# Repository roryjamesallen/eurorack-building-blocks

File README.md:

# eurorack-building-blocks
 A collection of building block circuits for eurorack

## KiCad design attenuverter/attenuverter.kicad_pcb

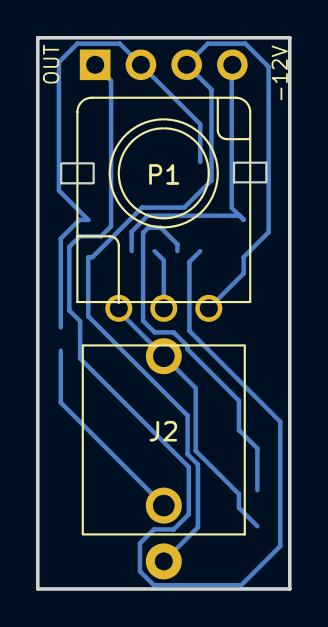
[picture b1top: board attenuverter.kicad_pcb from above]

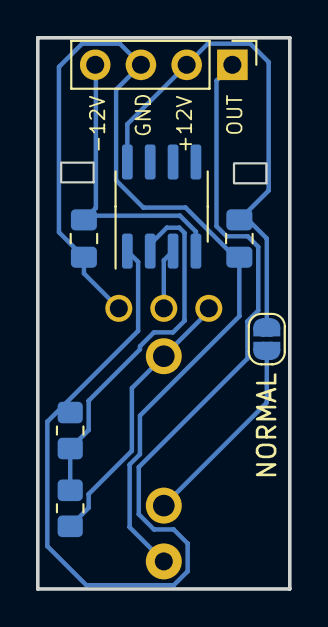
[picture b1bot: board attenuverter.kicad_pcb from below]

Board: 2 copper layers, 14.0 x 30.6 mm, 9 parts (7 on the bottom side), 8 nets.

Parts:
C1, C2: 100n; C_0805_2012Metric_Pad1.18x1.45mm_HandSolder
CONN1: Conn_01x04_Male; PinHeader_1x04_P2.54mm_Vertical
J2: Thonkiconn_Mono_Jack; Thonkiconn Mono Jack
JP1: SolderJumper_2_Open; SolderJumper-2_P1.3mm_Open_RoundedPad1.0x1.5mm
P1: Attenuverter; Potentiometer 9mm Vertical Linear Centred
R1, R2: 100K; R_0805_2012Metric_Pad1.20x1.40mm_HandSolder
U1: TL072; SOIC-8_3.9x4.9mm_P1.27mm

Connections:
+12V: C1.1, CONN1.2, JP1.2 (B), U1.8 (V+)
-12V: C2.2, CONN1.4, U1.4 (V-)
/OUT: CONN1.1, R2.2, U1.1
Earth: C1.2, C2.1, CONN1.3, J2.1 (E), P1.3
unnamed: J2.2 (TN), JP1.1 (A)
unnamed: J2.3 (T), P1.1, R1.1
unnamed: P1.2, U1.3 (+)
unnamed: R1.2, R2.1, U1.2 (-)

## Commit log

2022-05-12 KiCad Changes
